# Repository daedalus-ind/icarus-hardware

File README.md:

# Icarus Flight Computer V1.0

This repository contains the hardware design files for the version 1.0 of the flight computer developed for Project Icarus, a model rocket.

## 📸 Photos

## 🧰 Overview 

The Icarus Flight Computer V1.0 is designed to manage data acquisition, telemetry, and flight event control during rocket missions. The board includes:
- **Microcontroller**: STMicroelectronics STM32F405RGT6
- **6-Axis IMU**: TDK InvenSense ICM-45686
- **High-G Accelerometer**: Analog Devices ADXL375
- **Magnetometer**: STMicroelectronics LIS2MDL
- **Barometer**: MEAS MS5607
- **GPS Module**: u-blox NEO-M9N
- **Radio Module**: EBYTE E220-900T22S
- **Flash Memory**: Windbond W25Q128JV
- **E-matches**: 2x electric matches for recovery system deployment
- **Power Management**: TPS631000 buck-boost converter
- **Power Supply**: 1S LiPo battery or USB-C power input

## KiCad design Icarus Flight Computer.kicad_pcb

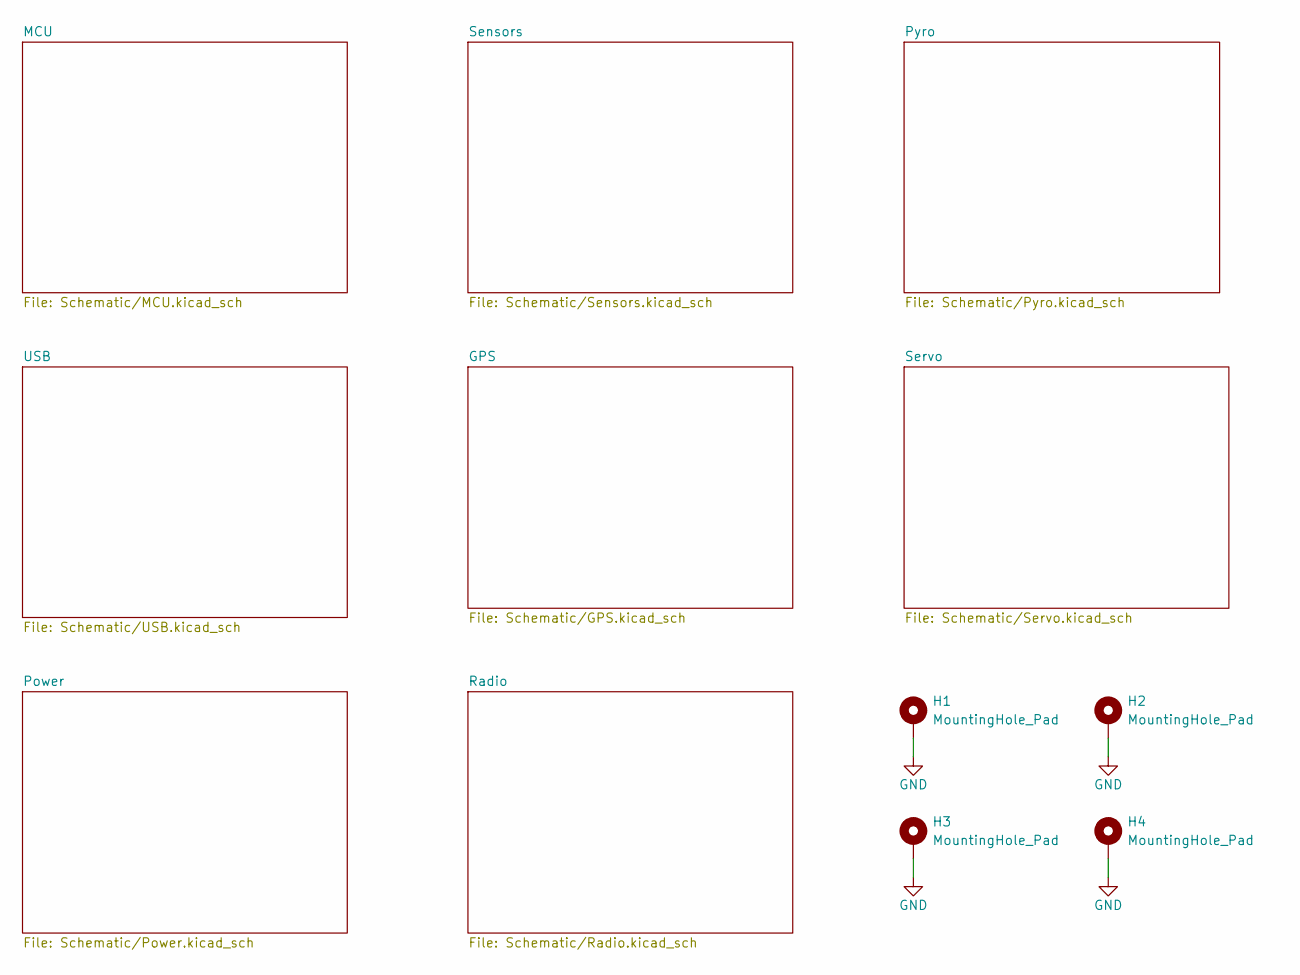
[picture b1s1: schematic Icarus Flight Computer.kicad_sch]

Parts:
H1, H2, H3, H4: MountingHole_Pad; MountingHole_2.7mm_M2.5_Pad_Via

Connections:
GND: H1.1, H2.1, H3.1, H4.1; also elsewhere on the board

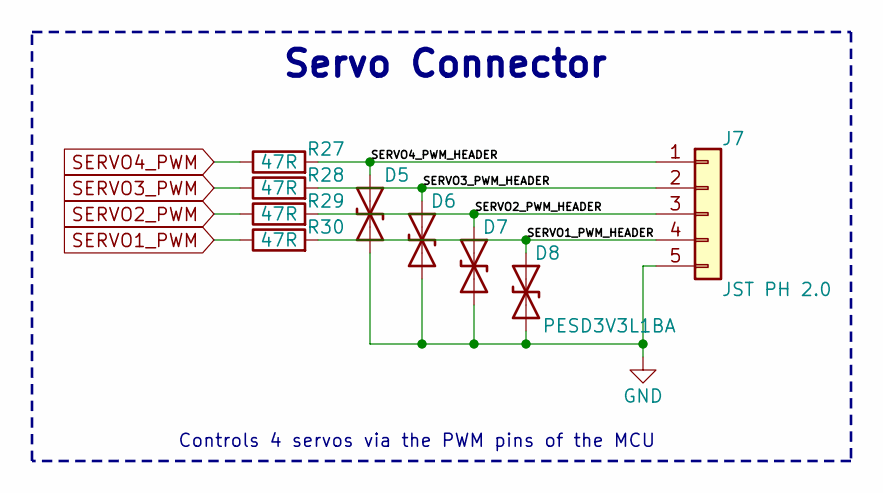
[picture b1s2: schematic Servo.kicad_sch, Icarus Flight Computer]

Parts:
D5, D6, D7, D8: PESD3V3L1BA; D_SOD-323; MPN C51450
J7: JST PH 2.0; JST_PH_B5B-PH-K_1x05_P2.00mm_Vertical; MPN C157993
R27, R28, R29, R30: 47R; R_0402_1005Metric; MPN C25118

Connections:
/Servo/SERVO1_PWM_HEADER: D8.1 (A1), J7.4, R30.2
/Servo/SERVO2_PWM_HEADER: D7.1 (A1), J7.3, R29.2
/Servo/SERVO3_PWM_HEADER: D6.1 (A1), J7.2, R28.2
/Servo/SERVO4_PWM_HEADER: D5.1 (A1), J7.1, R27.2
GND: D5.2 (A2), D6.2 (A2), D7.2 (A2), D8.2 (A2), J7.5; also elsewhere on the board
SERVO1_PWM: R30.1; also elsewhere on the board
SERVO2_PWM: R29.1; also elsewhere on the board
SERVO3_PWM: R28.1; also elsewhere on the board
SERVO4_PWM: R27.1; also elsewhere on the board

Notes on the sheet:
Servo Connector
Controls 4 servos via the PWM pins of the MCU

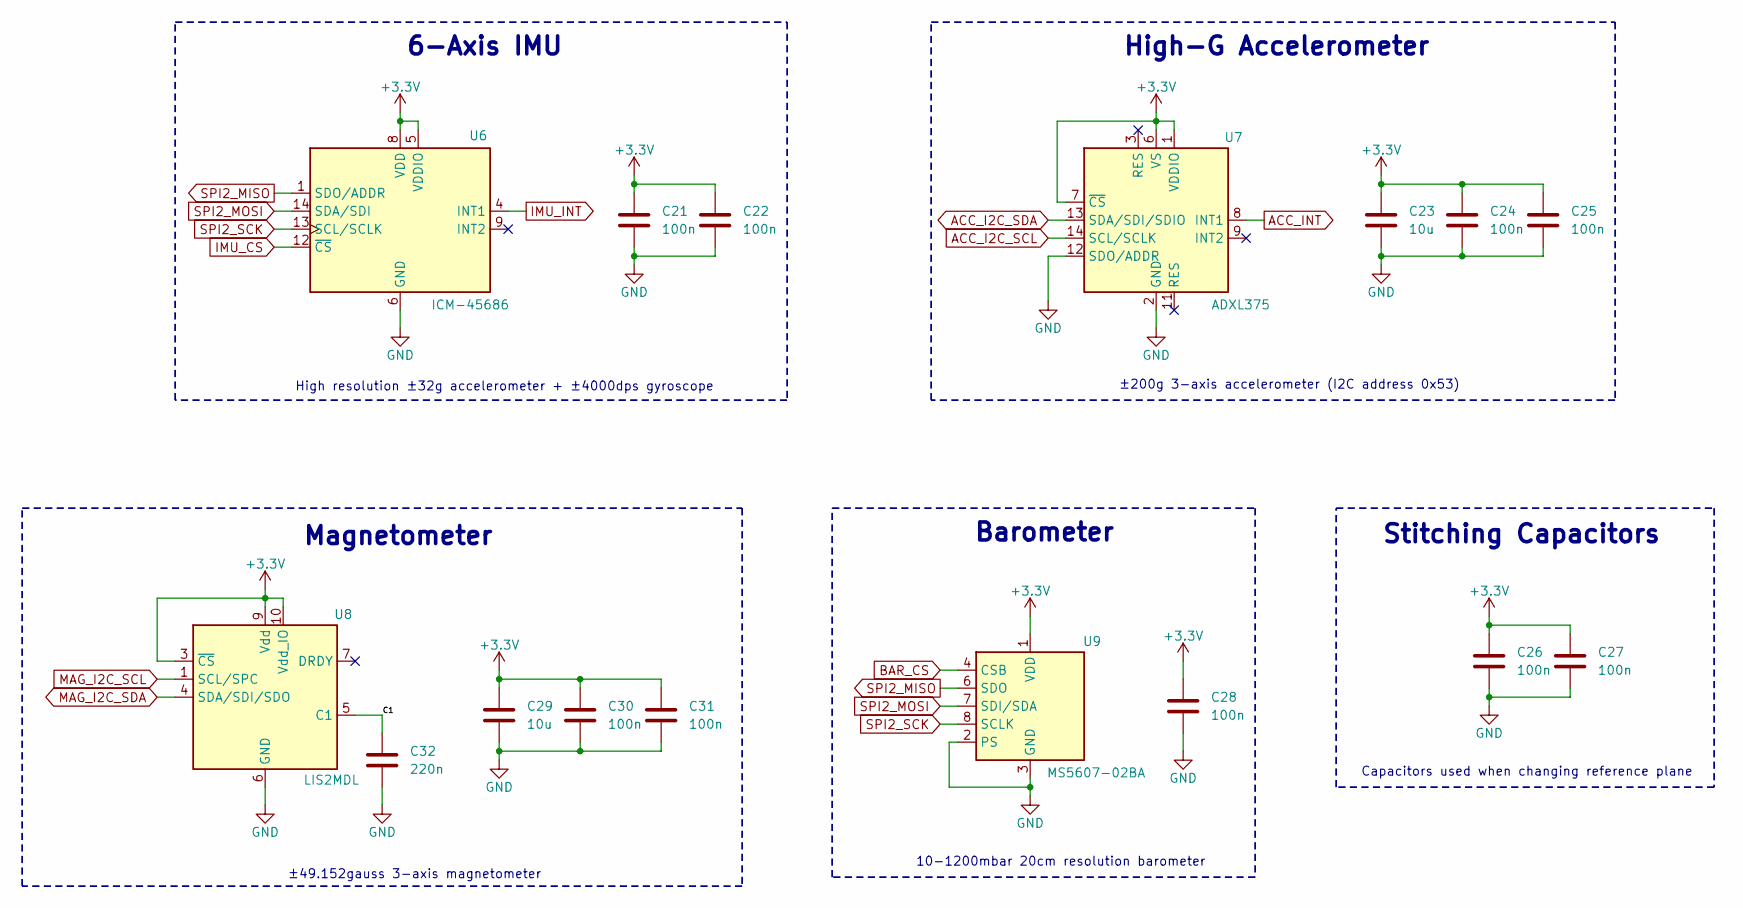
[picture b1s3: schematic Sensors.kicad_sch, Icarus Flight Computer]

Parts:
C21, C22, C24, C25, C26, C27, C28, C30, C31: 100n; C_0402_1005Metric; MPN C1525
C23, C29: 10u; C_0805_2012Metric; MPN C95841
C32: 220n; C_0402_1005Metric; MPN C16772
U6: ICM-45686; LGA-14_3x2.5mm_P0.5mm_LayoutBorder3x4y; MPN C22459454
U7: ADXL375; LGA-14_3x5mm_P0.8mm_LayoutBorder1x6y; MPN C579466
U8: LIS2MDL; LGA-12_2x2mm_P0.5mm; MPN C919695
U9: MS5607-02BA; MS5607-02BA03; MPN C97627

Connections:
+3.3V: C21.1, C22.1, C23.1, C24.1, C25.1, C26.1, C27.1, C28.1, C29.1, C30.1, C31.1, U6.5 (VDDIO), U6.8 (VDD), U7.1 (VDDIO), U7.6 (VS), U7.7 (~CS), U8.3 (~CS), U8.9 (Vdd), U8.10 (Vdd_IO), U9.1 (VDD); also elsewhere on the board
/Sensors/C1: C32.1, U8.5 (C1)
ACC_I2C_SCL: U7.14 (SCL/SCLK); also elsewhere on the board
ACC_I2C_SDA: U7.13 (SDA/SDI/SDIO); also elsewhere on the board
ACC_INT: U7.8 (INT1); also elsewhere on the board
BAR_CS: U9.4 (CSB), U9.5 (CSB); also elsewhere on the board
GND: C21.2, C22.2, C23.2, C24.2, C25.2, C26.2, C27.2, C28.2, C29.2, C30.2, C31.2, C32.2, U6.6 (GND), U7.2 (GND), U7.4 (GND), U7.5 (GND), U7.12 (SDO/ADDR), U8.6 (GND), U8.8 (GND), U9.2 (PS), U9.3 (GND); also elsewhere on the board
IMU_CS: U6.12 (~CS); also elsewhere on the board
IMU_INT: U6.4 (INT1); also elsewhere on the board
MAG_I2C_SCL: U8.1 (SCL/SPC); also elsewhere on the board
MAG_I2C_SDA: U8.4 (SDA/SDI/SDO); also elsewhere on the board
SPI2_MISO: U6.1 (SDO/ADDR), U9.6 (SDO); also elsewhere on the board
SPI2_MOSI: U6.14 (SDA/SDI), U9.7 (SDI/SDA); also elsewhere on the board
SPI2_SCK: U6.13 (SCL/SCLK), U9.8 (SCLK); also elsewhere on the board

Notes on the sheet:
±49.152gauss 3-axis magnetometer
Barometer
±200g 3-axis accelerometer (I2C address 0x53)
10-1200mbar 20cm resolution barometer
Magnetometer
High-G Accelerometer
6-Axis IMU
Capacitors used when changing reference plane
High resolution ±32g accelerometer + ±4000dps gyroscope
Stitching Capacitors

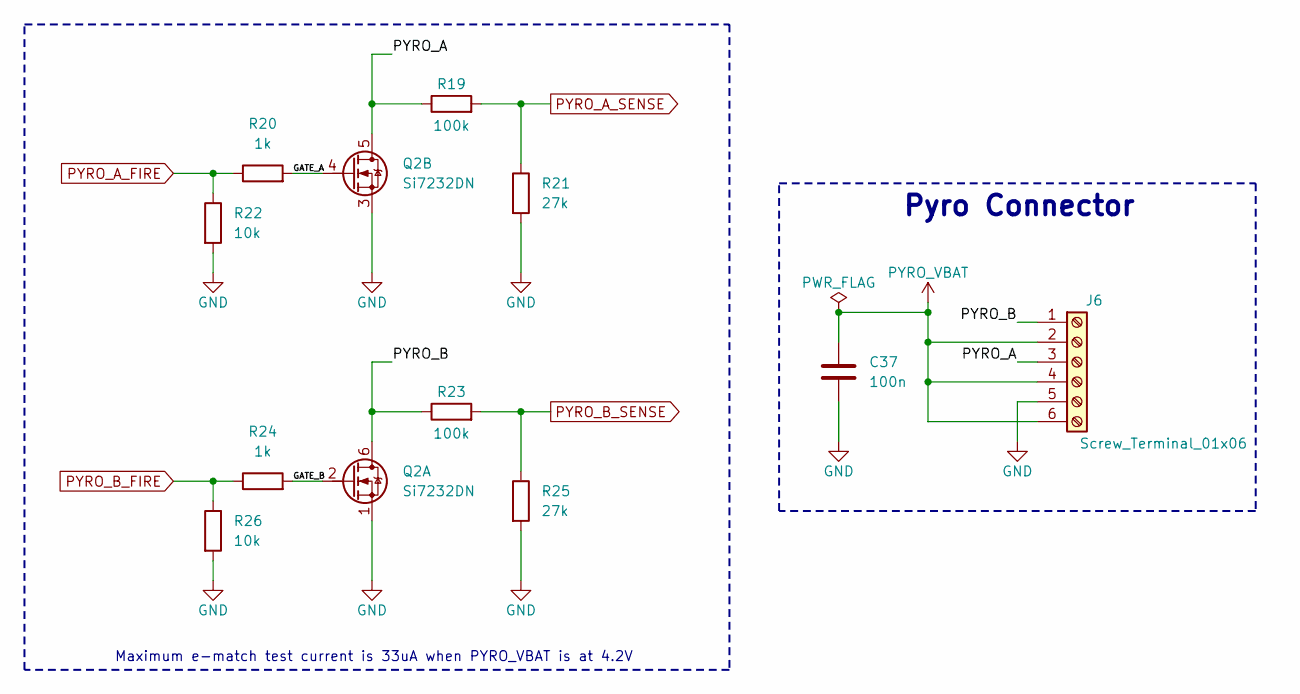
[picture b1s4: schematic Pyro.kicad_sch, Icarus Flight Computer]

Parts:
C37: 100n; C_0402_1005Metric; MPN C1525
J6: Screw_Terminal_01x06; TerminalBlock_Phoenix_MPT-0,5-6-2.54_1x06_P2.54mm_Horizontal; MPN C3817456
Q2: Si7232DN; Vishay_PowerPAK_1212-8_Dual; MPN C144854
R19, R23: 100k; R_0402_1005Metric; MPN C25741
R20, R24: 1k; R_0402_1005Metric; MPN C11702
R21, R25: 27k; R_0402_1005Metric; MPN C25771
R22, R26: 10k; R_0402_1005Metric; MPN C25531

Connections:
/Pyro/GATE_A: Q2.4 (G), R20.2
/Pyro/GATE_B: Q2.2 (G), R24.2
/Pyro/PYRO_A: J6.3, Q2.5 (D), R19.1
/Pyro/PYRO_B: J6.1, Q2.6 (D), R23.1
GND: C37.2, J6.5, Q2.1 (S), Q2.3 (S), R21.2, R22.2, R25.2, R26.2; also elsewhere on the board
PYRO_A_FIRE: R20.1, R22.1; also elsewhere on the board
PYRO_A_SENSE: R19.2, R21.1; also elsewhere on the board
PYRO_B_FIRE: R24.1, R26.1; also elsewhere on the board
PYRO_B_SENSE: R23.2, R25.1; also elsewhere on the board
PYRO_VBAT: C37.1, J6.2, J6.4, J6.6

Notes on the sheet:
Maximum e-match test current is 33uA when PYRO_VBAT is at 4.2V
Pyro Connector

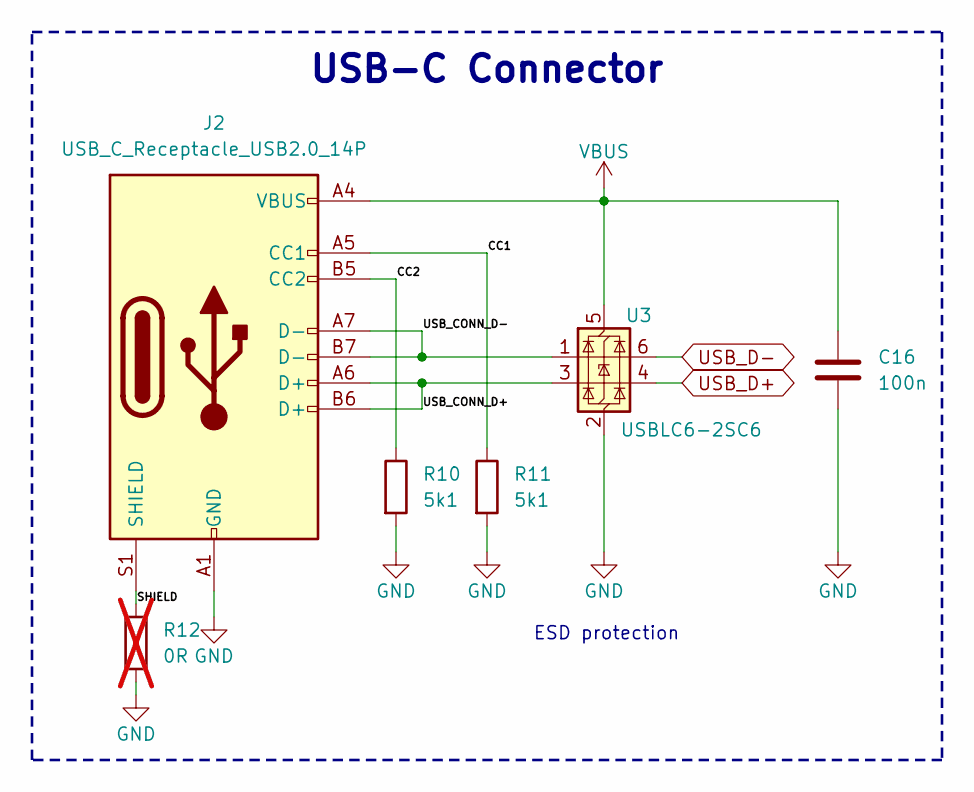
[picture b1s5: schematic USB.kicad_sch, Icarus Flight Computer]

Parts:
C16: 100n; C_0402_1005Metric; MPN C1525
J2: USB_C_Receptacle_USB2.0_14P; USB_C_Receptacle_G-Switch_GT-USB-7010ASV; MPN C2988369
R10, R11: 5k1; R_0402_1005Metric; MPN C25905
R12: 0R; R_0805_2012Metric; not fitted
U3: USBLC6-2SC6; SOT-23-6; MPN C7519

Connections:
/USB/CC1: J2.A5 (CC1), R11.1
/USB/CC2: J2.B5 (CC2), R10.1
/USB/SHIELD: J2.S1 (SHIELD), R12.1
/USB/USB_CONN_D+: J2.A6 (D+), J2.B6 (D+), U3.3 (I/O2)
/USB/USB_CONN_D-: J2.A7 (D-), J2.B7 (D-), U3.1 (I/O1)
GND: C16.2, J2.A1 (GND), J2.A12 (GND), J2.B1 (GND), J2.B12 (GND), R10.2, R11.2, R12.2, U3.2 (GND); also elsewhere on the board
USB_D+: U3.4 (I/O2); also elsewhere on the board
USB_D-: U3.6 (I/O1); also elsewhere on the board
VBUS: C16.1, J2.A4 (VBUS), J2.A9 (VBUS), J2.B4 (VBUS), J2.B9 (VBUS), U3.5 (VBUS); also elsewhere on the board

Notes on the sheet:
ESD protection
USB-C Connector

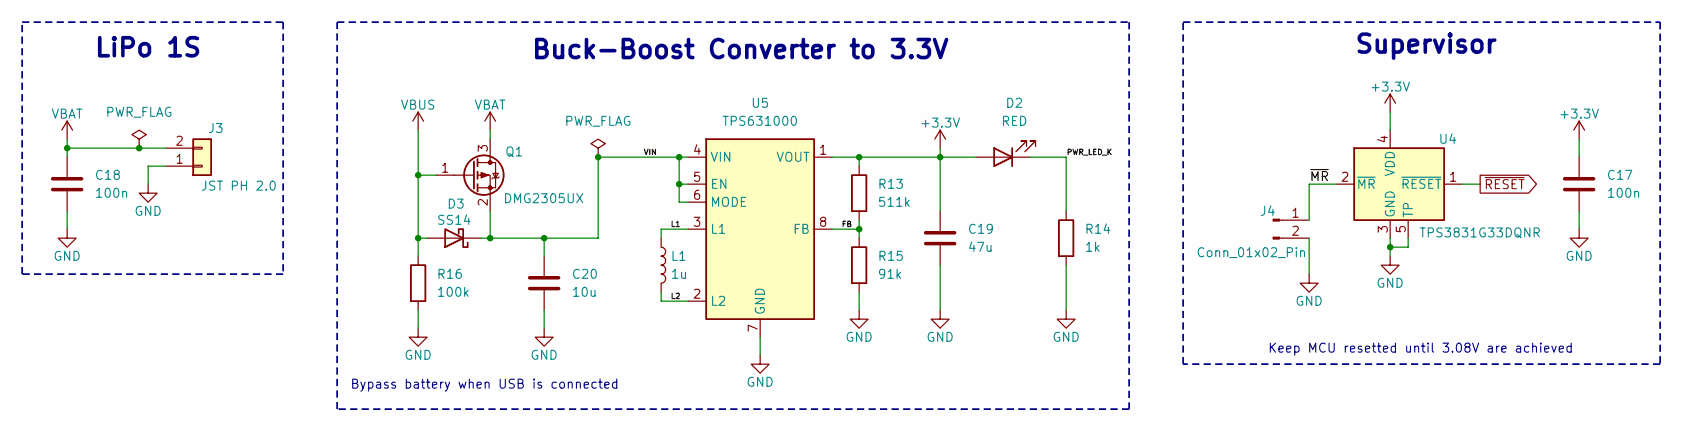
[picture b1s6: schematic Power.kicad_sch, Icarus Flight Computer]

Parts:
C17, C18: 100n; C_0402_1005Metric; MPN C1525
C19: 47u; C_0805_2012Metric; MPN C471380
C20: 10u; C_0603_1608Metric; MPN C90053
D2: RED; LED_0805_2012Metric; MPN C84256
D3: SS14; D_SMA; MPN C47460
J3: JST PH 2.0; JST_PH_B2B-PH-K_1x02_P2.00mm_Vertical; MPN C2683610
J4: Conn_01x02_Pin; PinHeader_1x02_P2.54mm_Vertical; MPN C492401
L1: 1u; L_1008_2520Metric; MPN C882955
Q1: DMG2305UX; SOT-23; MPN C150470
R13: 511k; R_0402_1005Metric; MPN C64042
R14: 1k; R_0402_1005Metric; MPN C11702
R15: 91k; R_0402_1005Metric; MPN C4147
R16: 100k; R_0402_1005Metric; MPN C25741
U4: TPS3831G33DQNR; Texas_X2SON-4_1x1mm_P0.65mm; MPN C2066649
U5: TPS631000; SOT-583-8; MPN C5219190

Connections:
+3.3V: C17.1, C19.1, D2.2 (A), R13.1, U4.4 (VDD), U5.1 (VOUT); also elsewhere on the board
/Power/FB: R13.2, R15.1, U5.8 (FB)
/Power/L1: L1.1, U5.3 (L1)
/Power/L2: L1.2, U5.2 (L2)
/Power/PWR_LED_K: D2.1 (K), R14.1
/Power/VIN: C20.1, D3.1 (K), Q1.2 (S), U5.4 (VIN), U5.5 (EN), U5.6 (MODE)
/Power/~MR: J4.1, U4.2 (~MR)
GND: C17.2, C18.2, C19.2, C20.2, J3.1, J4.2, R14.2, R15.2, R16.2, U4.3 (GND), U4.5 (TP), U5.7 (GND); also elsewhere on the board
VBAT: C18.1, J3.2, Q1.3 (D)
VBUS: D3.2 (A), Q1.1 (G), R16.1; also elsewhere on the board
~RESET: U4.1 (~RESET); also elsewhere on the board

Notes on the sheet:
Buck-Boost Converter to 3.3V
Keep MCU resetted until 3.08V are achieved
Supervisor
LiPo 1S
Bypass battery when USB is connected

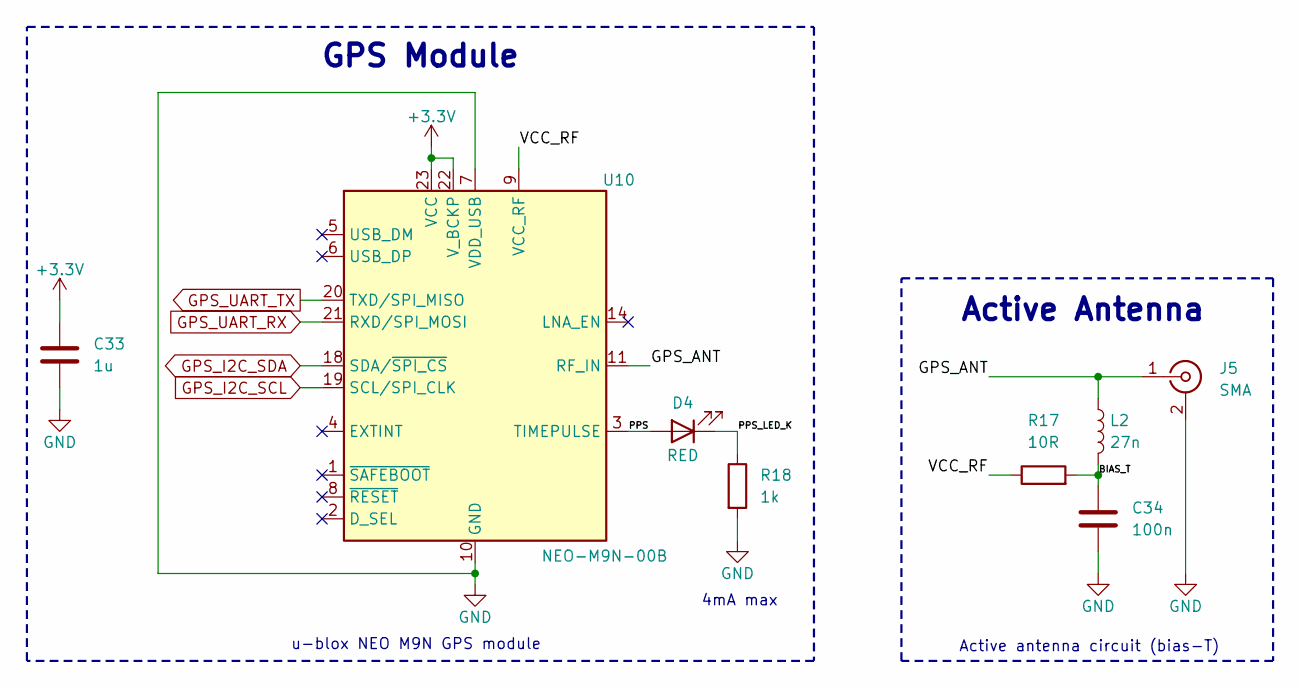
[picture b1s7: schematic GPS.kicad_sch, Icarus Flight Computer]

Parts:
C33: 1u; C_0603_1608Metric; MPN C59782
C34: 100n; C_0402_1005Metric; MPN C1525
D4: RED; LED_0805_2012Metric; MPN C84256
J5: SMA; SMA_Amphenol_132134_Vertical; MPN C3174425
L2: 27n; L_0402_1005Metric; MPN C12669
R17: 10R; R_1206_3216Metric; MPN C25349
R18: 1k; R_0402_1005Metric; MPN C11702
U10: NEO-M9N-00B; ublox_NEO; MPN C5119087

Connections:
+3.3V: C33.1, U10.22 (V_BCKP), U10.23 (VCC); also elsewhere on the board
/GPS/BIAS_T: C34.1, L2.2, R17.2
/GPS/GPS_ANT: J5.1 (In), L2.1, U10.11 (RF_IN)
/GPS/PPS: D4.2 (A), U10.3 (TIMEPULSE)
/GPS/PPS_LED_K: D4.1 (K), R18.1
/GPS/VCC_RF: R17.1, U10.9 (VCC_RF)
GND: C33.2, C34.2, J5.2 (Ext), R18.2, U10.7 (VDD_USB), U10.10 (GND), U10.12 (GND), U10.13 (GND), U10.24 (GND); also elsewhere on the board
GPS_I2C_SCL: U10.19 (SCL/SPI_CLK); also elsewhere on the board
GPS_I2C_SDA: U10.18 (SDA/~SPI_CS); also elsewhere on the board
GPS_UART_RX: U10.21 (RXD/SPI_MOSI); also elsewhere on the board
GPS_UART_TX: U10.20 (TXD/SPI_MISO); also elsewhere on the board

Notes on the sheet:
Active antenna circuit (bias-T)
u-blox NEO M9N GPS module
4mA max
Active Antenna
GPS Module

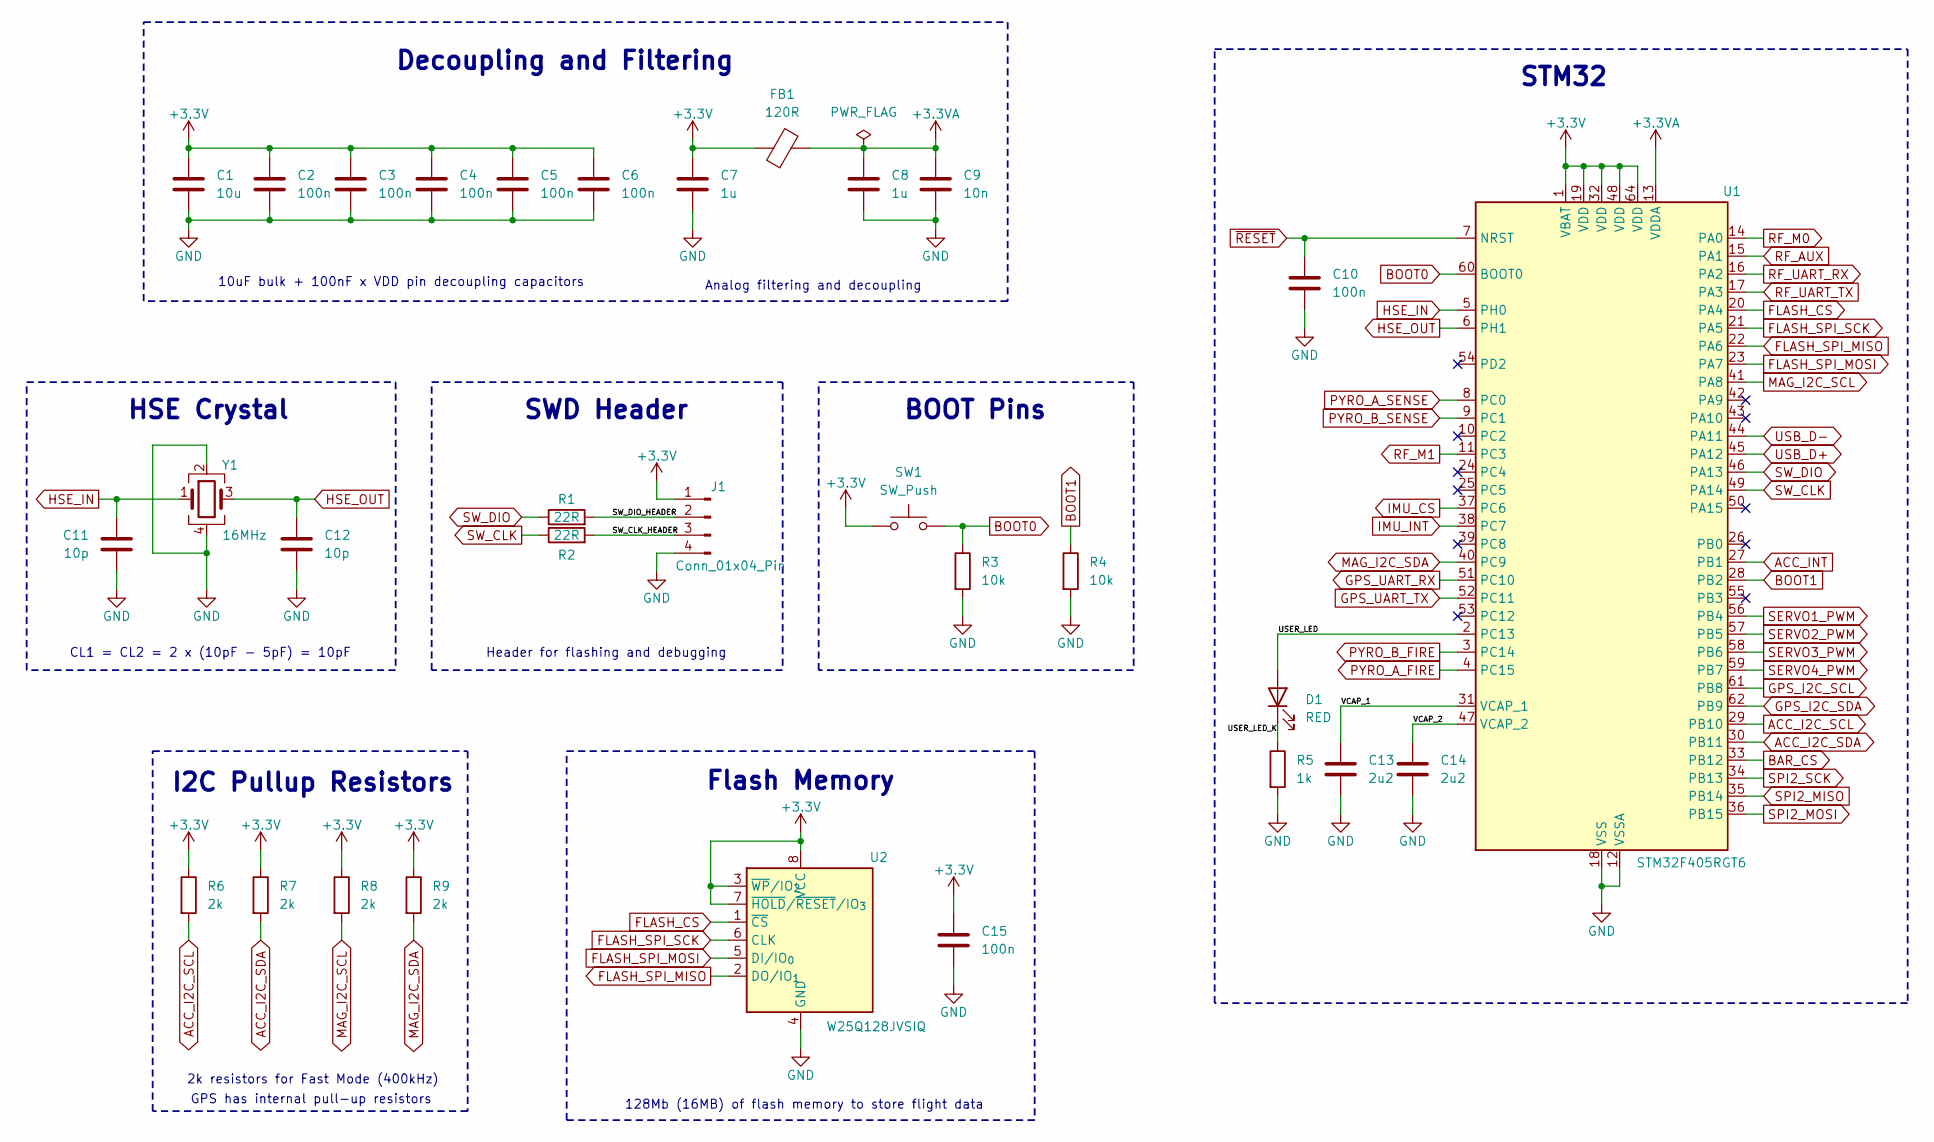
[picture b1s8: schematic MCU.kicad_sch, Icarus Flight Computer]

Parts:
C1: 10u; C_0805_2012Metric; MPN C95841
C2, C3, C4, C5, C6, C10, C15: 100n; C_0402_1005Metric; MPN C1525
C7, C8: 1u; C_0603_1608Metric; MPN C59782
C9: 10n; C_0402_1005Metric; MPN C318577
C11, C12: 10p; C_0402_1005Metric; MPN C32949
C13, C14: 2u2; C_0603_1608Metric; MPN C23630
D1: RED; LED_0805_2012Metric; MPN C84256
FB1: 120R; L_0603_1608Metric; MPN C85831
J1: Conn_01x04_Pin; PinHeader_1x04_P2.54mm_Vertical; MPN C2691448
R1, R2: 22R; R_0402_1005Metric; MPN C25092
R3, R4: 10k; R_0402_1005Metric; MPN C25531
R5: 1k; R_0402_1005Metric; MPN C11702
R6, R7, R8, R9: 2k; R_0402_1005Metric; MPN C4109
SW1: SW_Push; SW_TS-1088-AR02016; MPN C720477
U1: STM32F405RGT6; LQFP-64_10x10mm_P0.5mm; MPN C15742
U2: W25Q128JVSIQ; SOIC-8_5.3x5.3mm_P1.27mm; MPN C97521
Y1: 16MHz; Crystal_SMD_3225-4Pin_3.2x2.5mm; MPN C112972

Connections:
+3.3V: C1.1, C2.1, C3.1, C4.1, C5.1, C6.1, C7.1, C15.1, FB1.1, J1.1, R6.1, R7.1, R8.1, R9.1, SW1.1, U1.1 (VBAT), U1.19 (VDD), U1.32 (VDD), U1.48 (VDD), U1.64 (VDD), U2.3 (~WP/IO_{2}), U2.7 (~HOLD/~RESET/IO_{3}), U2.8 (VCC); also elsewhere on the board
+3.3VA: C8.1, C9.1, FB1.2, U1.13 (VDDA)
/MCU/SW_CLK_HEADER: J1.3, R2.2
/MCU/SW_DIO_HEADER: J1.2, R1.2
/MCU/USER_LED: D1.2 (A), U1.2 (PC13)
/MCU/USER_LED_K: D1.1 (K), R5.1
/MCU/VCAP_1: C13.1, U1.31 (VCAP_1)
/MCU/VCAP_2: C14.1, U1.47 (VCAP_2)
ACC_I2C_SCL: R6.2, U1.29 (PB10); also elsewhere on the board
ACC_I2C_SDA: R7.2, U1.30 (PB11); also elsewhere on the board
ACC_INT: U1.27 (PB1); also elsewhere on the board
BAR_CS: U1.33 (PB12); also elsewhere on the board
BOOT0: R3.1, SW1.2, U1.60 (BOOT0)
BOOT1: R4.1, U1.28 (PB2)
FLASH_CS: U1.20 (PA4), U2.1 (~CS)
FLASH_SPI_MISO: U1.22 (PA6), U2.2 (DO/IO_{1})
FLASH_SPI_MOSI: U1.23 (PA7), U2.5 (DI/IO_{0})
FLASH_SPI_SCK: U1.21 (PA5), U2.6 (CLK)
GND: C1.2, C2.2, C3.2, C4.2, C5.2, C6.2, C7.2, C8.2, C9.2, C10.2, C11.2, C12.2, C13.2, C14.2, C15.2, J1.4, R3.2, R4.2, R5.2, U1.12 (VSSA), U1.18 (VSS), U1.63 (VSS), U2.4 (GND), Y1.2, Y1.4; also elsewhere on the board
GPS_I2C_SCL: U1.61 (PB8); also elsewhere on the board
GPS_I2C_SDA: U1.62 (PB9); also elsewhere on the board
GPS_UART_RX: U1.51 (PC10); also elsewhere on the board
GPS_UART_TX: U1.52 (PC11); also elsewhere on the board
HSE_IN: C11.1, U1.5 (PH0), Y1.1
HSE_OUT: C12.1, U1.6 (PH1), Y1.3
IMU_CS: U1.37 (PC6); also elsewhere on the board
IMU_INT: U1.38 (PC7); also elsewhere on the board
MAG_I2C_SCL: R8.2, U1.41 (PA8); also elsewhere on the board
MAG_I2C_SDA: R9.2, U1.40 (PC9); also elsewhere on the board
PYRO_A_FIRE: U1.4 (PC15); also elsewhere on the board
PYRO_A_SENSE: U1.8 (PC0); also elsewhere on the board
PYRO_B_FIRE: U1.3 (PC14); also elsewhere on the board
PYRO_B_SENSE: U1.9 (PC1); also elsewhere on the board
RF_AUX: U1.15 (PA1); also elsewhere on the board
RF_M0: U1.14 (PA0); also elsewhere on the board
RF_M1: U1.11 (PC3); also elsewhere on the board
RF_UART_RX: U1.16 (PA2); also elsewhere on the board
RF_UART_TX: U1.17 (PA3); also elsewhere on the board
SERVO1_PWM: U1.56 (PB4); also elsewhere on the board
SERVO2_PWM: U1.57 (PB5); also elsewhere on the board
SERVO3_PWM: U1.58 (PB6); also elsewhere on the board
SERVO4_PWM: U1.59 (PB7); also elsewhere on the board
SPI2_MISO: U1.35 (PB14); also elsewhere on the board
SPI2_MOSI: U1.36 (PB15); also elsewhere on the board
SPI2_SCK: U1.34 (PB13); also elsewhere on the board
SW_CLK: R2.1, U1.49 (PA14)
SW_DIO: R1.1, U1.46 (PA13)
USB_D+: U1.45 (PA12); also elsewhere on the board
USB_D-: U1.44 (PA11); also elsewhere on the board
~RESET: C10.1, U1.7 (NRST); also elsewhere on the board

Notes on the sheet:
Analog filtering and decoupling
I2C Pullup Resistors
STM32
Flash Memory
HSE Crystal
GPS has internal pull-up resistors
BOOT Pins
CL1 = CL2 = 2 x (10pF - 5pF) = 10pF
10uF bulk + 100nF x VDD pin decoupling capacitors
128Mb (16MB) of flash memory to store flight data
2k resistors for Fast Mode (400kHz)
SWD Header
Decoupling and Filtering
Header for flashing and debugging

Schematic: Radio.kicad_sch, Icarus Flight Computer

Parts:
C35: 10u; C_0805_2012Metric; MPN C95841
C36: 100n; C_0402_1005Metric; MPN C1525
U11: E220-900T22S; E220-xxxT22S; MPN C970285

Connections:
+3.3V: C35.1, C36.1, U11.25 (VCC); also elsewhere on the board
GND: C35.2, C36.2, U11.2 (GND), U11.8 (GND), U11.11 (GND), U11.13 (GND), U11.14 (GND), U11.15 (GND), U11.16 (GND), U11.19 (GND), U11.26 (GND); also elsewhere on the board
RF_AUX: U11.24 (AUX); also elsewhere on the board
RF_M0: U11.20 (M0); also elsewhere on the board
RF_M1: U11.21 (M1); also elsewhere on the board
RF_UART_RX: U11.22 (RXD); also elsewhere on the board
RF_UART_TX: U11.23 (TXD); also elsewhere on the board

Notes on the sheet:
62.5kbps LoRa communication module
LoRa Radio

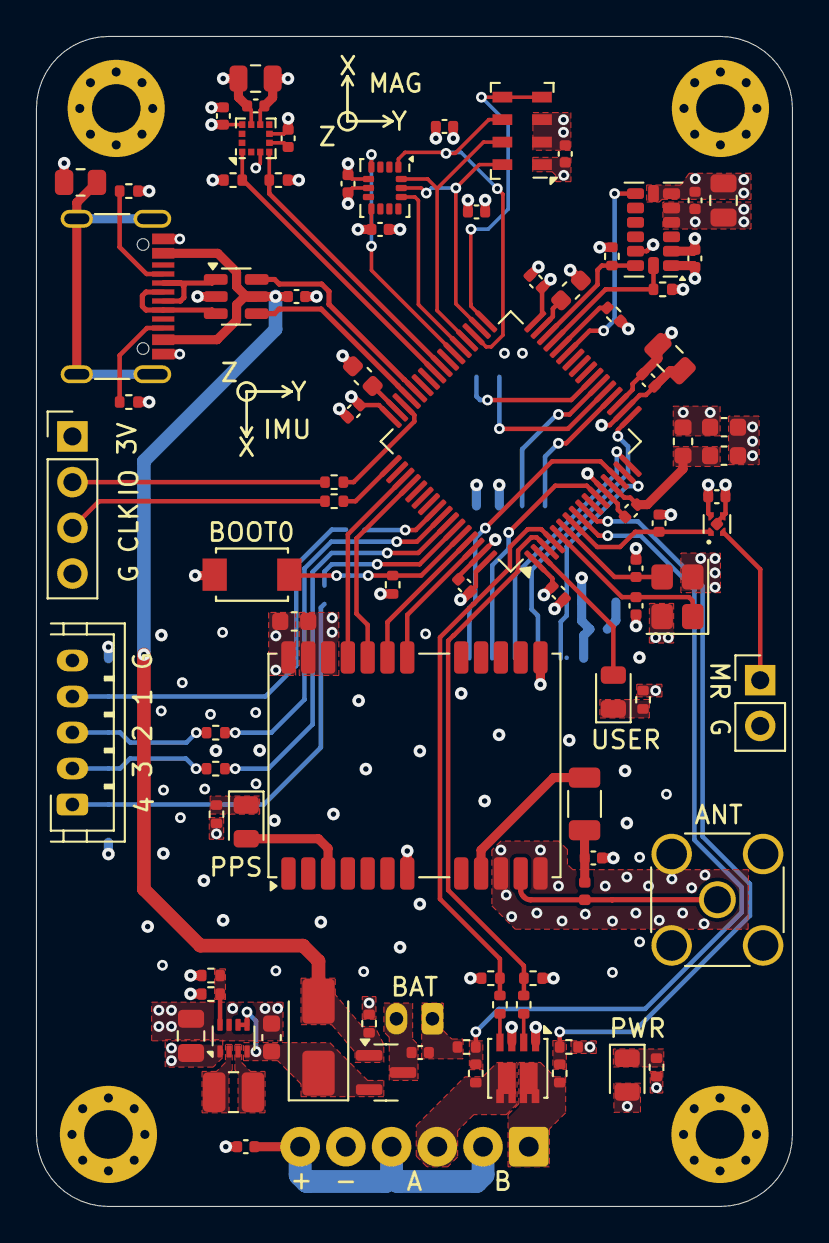
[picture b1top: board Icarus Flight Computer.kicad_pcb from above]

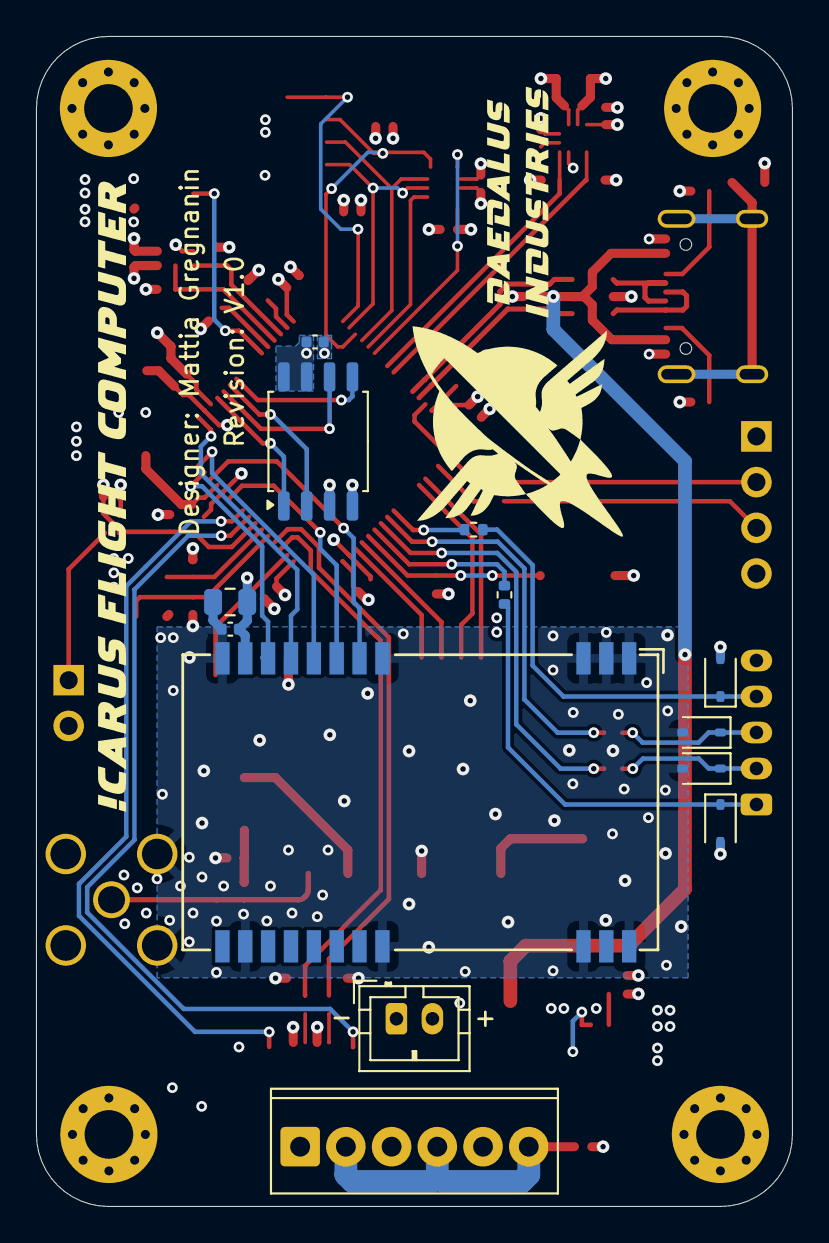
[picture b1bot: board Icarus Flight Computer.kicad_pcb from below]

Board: 4 copper layers, 42.0 x 65.0 mm, 104 parts (13 on the bottom side), 78 nets.

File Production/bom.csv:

Designator,Footprint,Quantity,Value,LCSC Part #
"C1, C23, C29, C35",0805,4,10u,C95841
"C10, C15, C16, C17, C18, C2, C21, C22, C24, C25, C26, C27, C28, C3, C30, C31, C34, C36, C37, C4, C5, C6",0402,22,100n,C1525
"C11, C12",0402,2,10p,C32949
"C13, C14",0603,2,2u2,C23630
C19,0805,1,47u,C471380
C20,0603,1,10u,C90053
C32,0402,1,220n,C16772
"C33, C7, C8",0603,3,1u,C59782
C9,0402,1,10n,C318577
"D1, D2, D4",0805,3,RED,C84256
D3,D_SMA,1,SS14,C47460
"D5, D6, D7, D8",D_SOD-323,4,PESD3V3L1BA,C51450
FB1,0603,1,120R,C85831
J1,PinHeader_1x04_P2.54mm_Vertical,1,Conn_01x04_Pin,C2691448
J2,USB_C_Receptacle_G-Switch_GT-USB-7010ASV,1,USB_C_Receptacle_USB2.0_14P,C2988369
J3,JST_PH_B2B-PH-K_1x02_P2.00mm_Vertical,1,JST PH 2.0,C2683610
J4,PinHeader_1x02_P2.54mm_Vertical,1,Conn_01x02_Pin,C492401
J5,SMA_Amphenol_132134_Vertical,1,SMA,C3174425
J6,"TerminalBlock_Phoenix_MPT-0,5-6-2.54_1x06_P2.54mm_Horizontal",1,Screw_Terminal_01x06,C3817456
J7,JST_PH_B5B-PH-K_1x05_P2.00mm_Vertical,1,JST PH 2.0,C157993
L1,1008,1,1u,C882955
L2,0402,1,27n,C12669
Q1,SOT-23,1,DMG2305UX,C150470
Q2,Vishay_PowerPAK_1212-8_Dual,1,Si7232DN,C144854
"R1, R2",0402,2,22R,C25092
"R10, R11",0402,2,5k1,C25905
R13,0402,1,511k,C64042
"R14, R18, R20, R24, R5",0402,5,1k,C11702
R15,0402,1,91k,C4147
"R16, R19, R23",0402,3,100k,C25741
R17,1206,1,10R,C25349
"R21, R25",0402,2,27k,C25771
"R22, R26, R3, R4",0402,4,10k,C25531
"R27, R28, R29, R30",0402,4,47R,C25118
"R6, R7, R8, R9",0402,4,2k,C4109
SW1,SW_TS-1088-AR02016,1,SW_Push,C720477
U1,LQFP-64_10x10mm_P0.5mm,1,STM32F405RGT6,C15742
U10,ublox_NEO,1,NEO-M9N-00B,C5119087
U11,E220-xxxT22S,1,E220-900T22S,C970285
U2,SOIC-8_5.3x5.3mm_P1.27mm,1,W25Q128JVSIQ,C97521
U3,SOT-23-6,1,USBLC6-2SC6,C7519
U4,Texas_X2SON-4_1x1mm_P0.65mm,1,TPS3831G33DQNR,C2066649
U5,SOT-583-8,1,TPS631000,C5219190
U6,LGA-14_3x2.5mm_P0.5mm_LayoutBorder3x4y,1,ICM-45686,C22459454
U7,LGA-14_3x5mm_P0.8mm_LayoutBorder1x6y,1,ADXL375,C579466
U8,LGA-12_2x2mm_P0.5mm,1,LIS2MDL,C919695
U9,MS5607-02BA03,1,MS5607-02BA,C97627
Y1,Crystal_SMD_3225-4Pin_3.2x2.5mm,1,16MHz,C112972

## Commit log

2025-05-07 Added files
2025-05-07 Added Docs folder
2025-05-16 Made board smaller
2025-05-21 V1.0
2025-06-03 Added README.md with photos
